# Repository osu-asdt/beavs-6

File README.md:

# BEAVS 6.7
BEAVS is a rocketry flight computer, with a comprehensive sensor suite and five servo channels.

## Features
- IMU
- Barometer
- Magnetometer
- Five 8.4V 10A servo channels with current monitoring
- Status LEDs
- Reverse polarity protection

## Parts
- RP2040 microcontroller
- ISM6HG256X IMU
- MS5607 barometer
- LIS2MDL magnetometer
- INA745 current monitors

## Pinout
| GPIO | Function            |
|------|---------------------|
|    0 | MISO                |
|    2 | SCK                 |
|    3 | MOSI                |
|    1 | Barometer CS        |
|    6 | IMU CS              |
|    4 | SDA                 |
|    5 | SCL                 |
|    7 | SD CMD              |
|    8 | SD DAT0             |
|    9 | SD DAT1             |
|   10 | SD DAT2             |
|   11 | SD DAT3             |
|   12 | SD CLK              |
|   14 | Expansion 1 (SDA)   |
|   15 | Expansion 2 (SCL)   |
|   13 | UART RX             |
|   16 | UART TX             |
|   17 | Servo power enable  |
|   28 | Efuse current       |
|   19 | Efuse status        |
|   27 | Servo 1             |
|   23 | Servo 2             |
|   24 | Servo 3             |
|   25 | Servo 4             |
|   26 | Servo 5             |
|   29 | Battery sense       |
|   22 | LED data            |
|   18 | Levelshift dir      |
|   21 | Arm switch          |

## Addresses
| Name             | Part     | I2C Address |
|------------------|----------|-------------|
| Magnetometer     | LIS2MDL  | 0x1e        |
| Servo 1 monitor  | INA745   | 0x40        |
| Servo 2 monitor  | INA745   | 0x41        |
| Servo 3 monitor  | INA745   | 0x43        |
| Servo 4 monitor  | INA745   | 0x44        |
| Servo 5 monitor  | INA745   | 0x45        |

## Notes
- The servo power enable pin is active high
- The boot and reset button on the board are enabled by the jumper J14 on the top right side of the board, this jumper must be removed before flight
- The servo pins are, from the center of the board to the edge, signal, ground, power
- The levelshift dir pin should be low in normal operation, and never floating
- The servo data pins and LED data pin should never be floating
- The arming switch should have an internal pullup, and closing the switch connects the pin to ground
- The battery sense pin is connected through a 100k-51k voltage divider, so the pin voltage is 0.3311 times the battery voltage
- Each servo channel can measure up to 39A, but continuous current shouldn't go much above 10A
- The total current consumption should be below 15A continuous
- The efuse current limit is set to 17.6A
- The addressable LEDs are WS2812-compatible, and they are chained as follows: status, magnetometer, barometer, IMU, SD
- The board can be configured to act as a USB host by swapping the CC resistors and adding a jumper, see the schematic

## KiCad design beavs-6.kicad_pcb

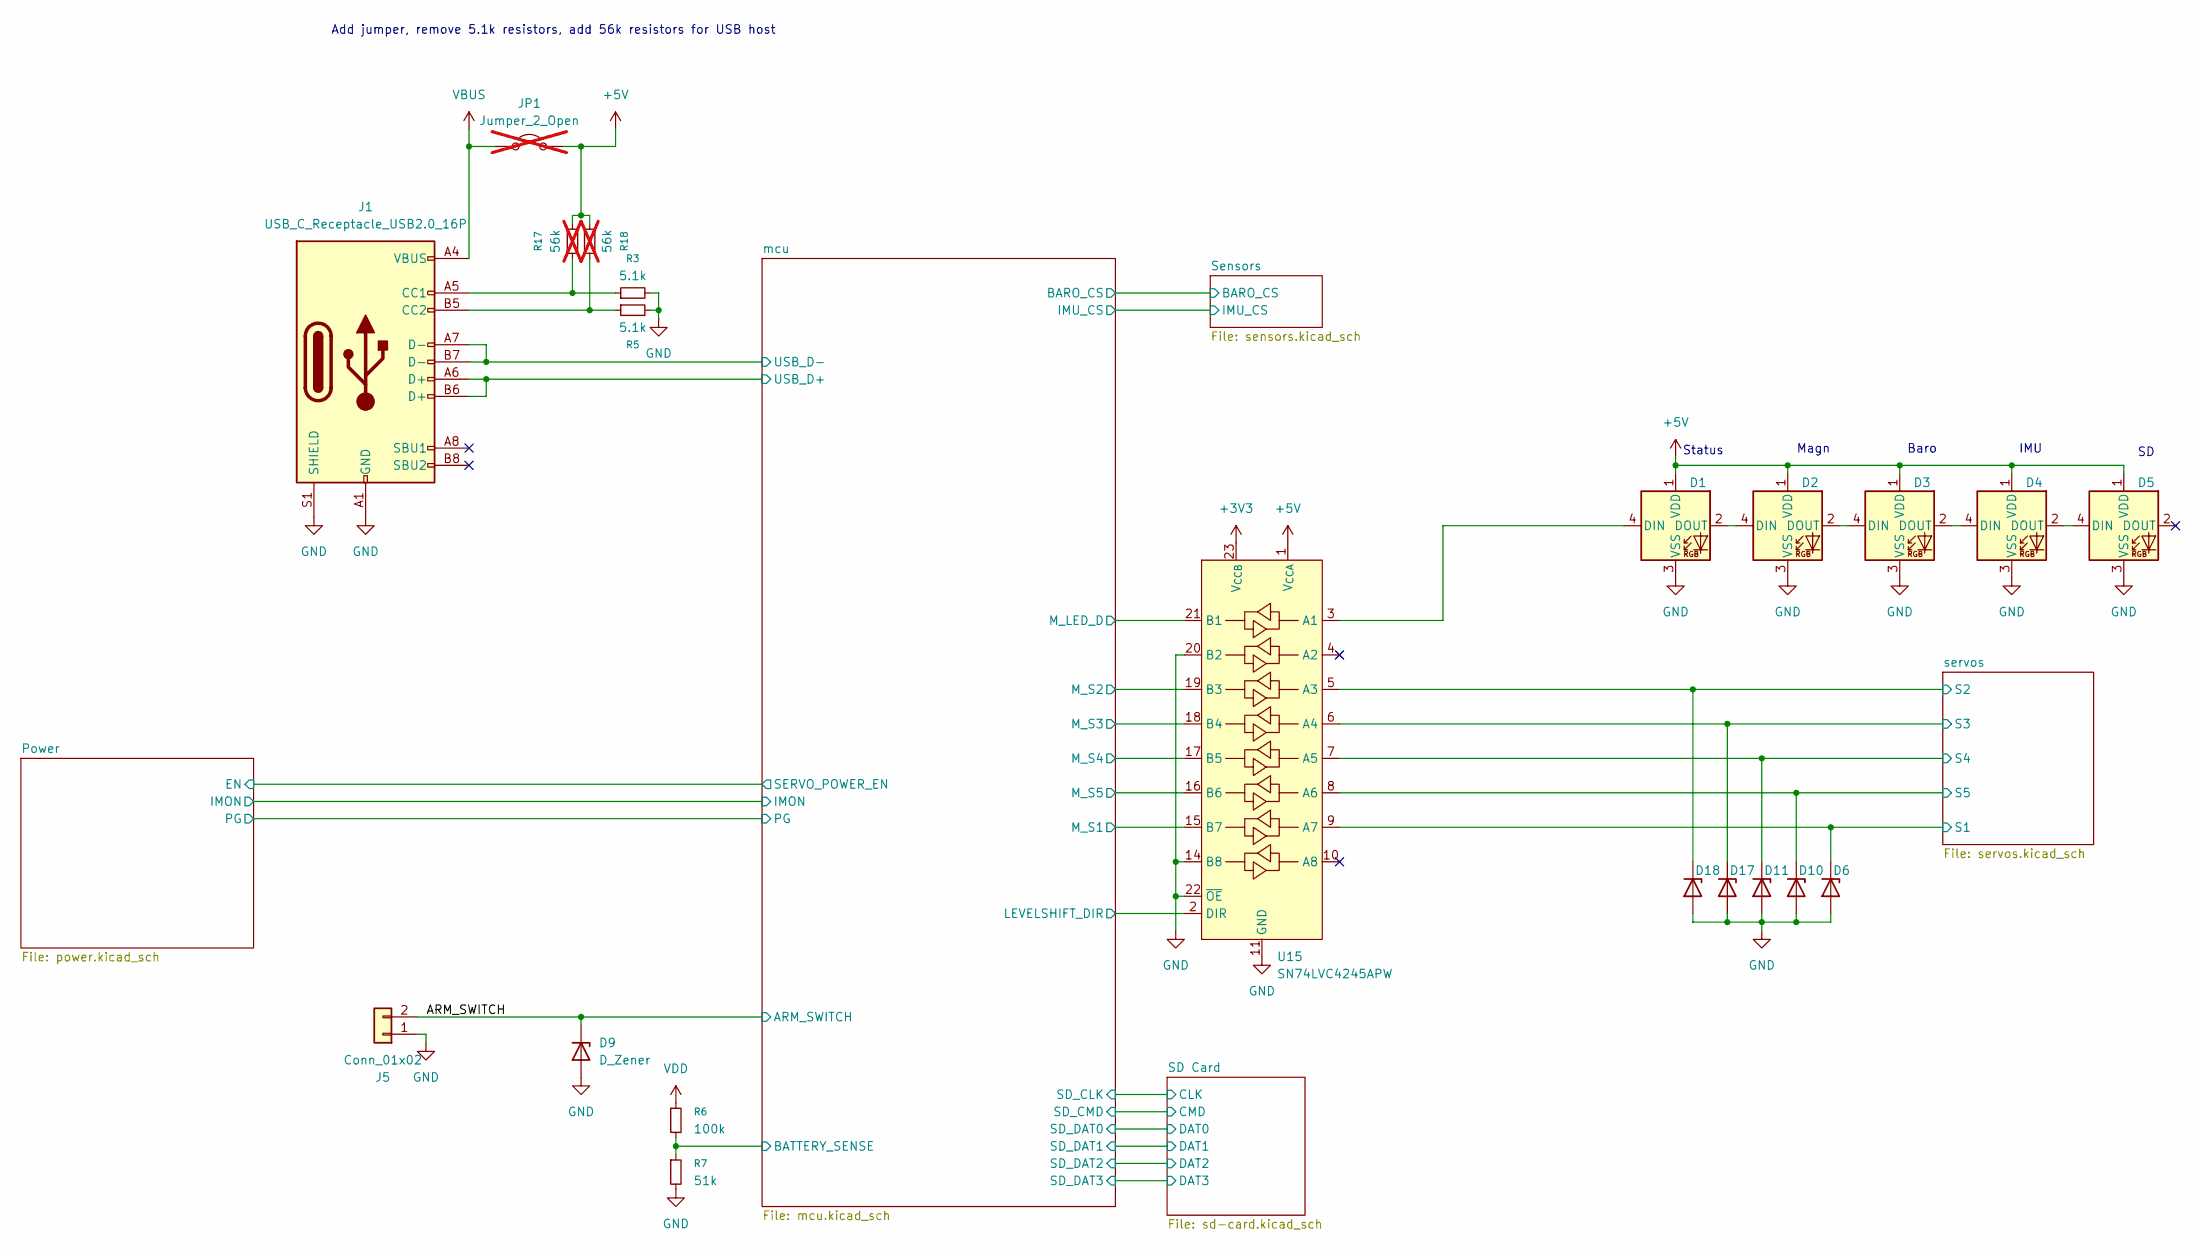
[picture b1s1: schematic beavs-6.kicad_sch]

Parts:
D1, D2, D3, D4, D5: SK6812-EC20; LED_SK6812-EC20_PLCC4_2.0x2.0mm; LCSC C2909058
D6, D10, D11, D17, D18: D_Zener; D_SOD-523; LCSC C20615819
D9: D_Zener; D_SOD-323; LCSC C20615801
J1: USB_C_Receptacle_USB2.0_16P; USB_C_Receptacle_G-Switch_GT-USB-7010ASV; LCSC C2988369
J5: Conn_01x02; JST_PH_B2B-PH-K_1x02_P2.00mm_Vertical; digikey 455-1704-ND
JP1: Jumper_2_Open; R_0402_1005Metric; not fitted
R3, R5: 5.1k; R_0402_1005Metric; LCSC C25905
R6: 100k; R_0402_1005Metric; LCSC C25741
R7: 51k; R_0402_1005Metric; LCSC C25794
R17, R18: 56k; R_0402_1005Metric; not fitted
U15: SN74LVC4245APW; TSSOP-24_4.4x7.8mm_P0.65mm; LCSC C7859

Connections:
+3V3: U15.23 (V_{CCB}), U15.24 (V_{CCB}); also elsewhere on the board
+5V: D1.1 (VDD), D2.1 (VDD), D3.1 (VDD), D4.1 (VDD), D5.1 (VDD), JP1.2 (B), R17.1, R18.1, U15.1 (V_{CCA}); also elsewhere on the board
/ARM_SWITCH: D9.1 (K), J5.2; also elsewhere on the board
/mcu/BATTERY_SENSE: R6.2, R7.1; also elsewhere on the board
/mcu/LEVELSHIFT_DIR: U15.2 (DIR); also elsewhere on the board
/mcu/M_LED_D: U15.21 (B1); also elsewhere on the board
/mcu/M_S1: U15.15 (B7); also elsewhere on the board
/mcu/M_S2: U15.19 (B3); also elsewhere on the board
/mcu/M_S3: U15.18 (B4); also elsewhere on the board
/mcu/M_S4: U15.17 (B5); also elsewhere on the board
/mcu/M_S5: U15.16 (B6); also elsewhere on the board
/mcu/USB_D+: J1.A6 (D+), J1.B6 (D+); also elsewhere on the board
/mcu/USB_D-: J1.A7 (D-), J1.B7 (D-); also elsewhere on the board
/servos/S1: D6.1 (K), U15.9 (A7); also elsewhere on the board
/servos/S2: D18.1 (K), U15.5 (A3); also elsewhere on the board
/servos/S3: D17.1 (K), U15.6 (A4); also elsewhere on the board
/servos/S4: D11.1 (K), U15.7 (A5); also elsewhere on the board
/servos/S5: D10.1 (K), U15.8 (A6); also elsewhere on the board
GND: D1.3 (VSS), D2.3 (VSS), D3.3 (VSS), D4.3 (VSS), D5.3 (VSS), D6.2 (A), D9.2 (A), D10.2 (A), D11.2 (A), D17.2 (A), D18.2 (A), J1.A1 (GND), J1.A12 (GND), J1.B1 (GND), J1.B12 (GND), J1.S1 (SHIELD), J5.1, R3.2, R5.2, R7.2, U15.11 (GND), U15.12 (GND), U15.13 (GND), U15.14 (B8), U15.20 (B2), U15.22 (~OE); also elsewhere on the board
unnamed: D1.4 (DIN), U15.3 (A1)
unnamed: D1.2 (DOUT), D2.4 (DIN)
unnamed: D2.2 (DOUT), D3.4 (DIN)
unnamed: D3.2 (DOUT), D4.4 (DIN)
unnamed: D4.2 (DOUT), D5.4 (DIN)
unnamed: J1.A5 (CC1), R3.1, R17.2
unnamed: J1.B5 (CC2), R5.1, R18.2
VBUS: J1.A4 (VBUS), J1.A9 (VBUS), J1.B4 (VBUS), J1.B9 (VBUS), JP1.1 (A); also elsewhere on the board
VDD: R6.1; also elsewhere on the board

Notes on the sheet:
Add jumper, remove 5.1k resistors, add 56k resistors for USB host
Baro
IMU
Status
Magn

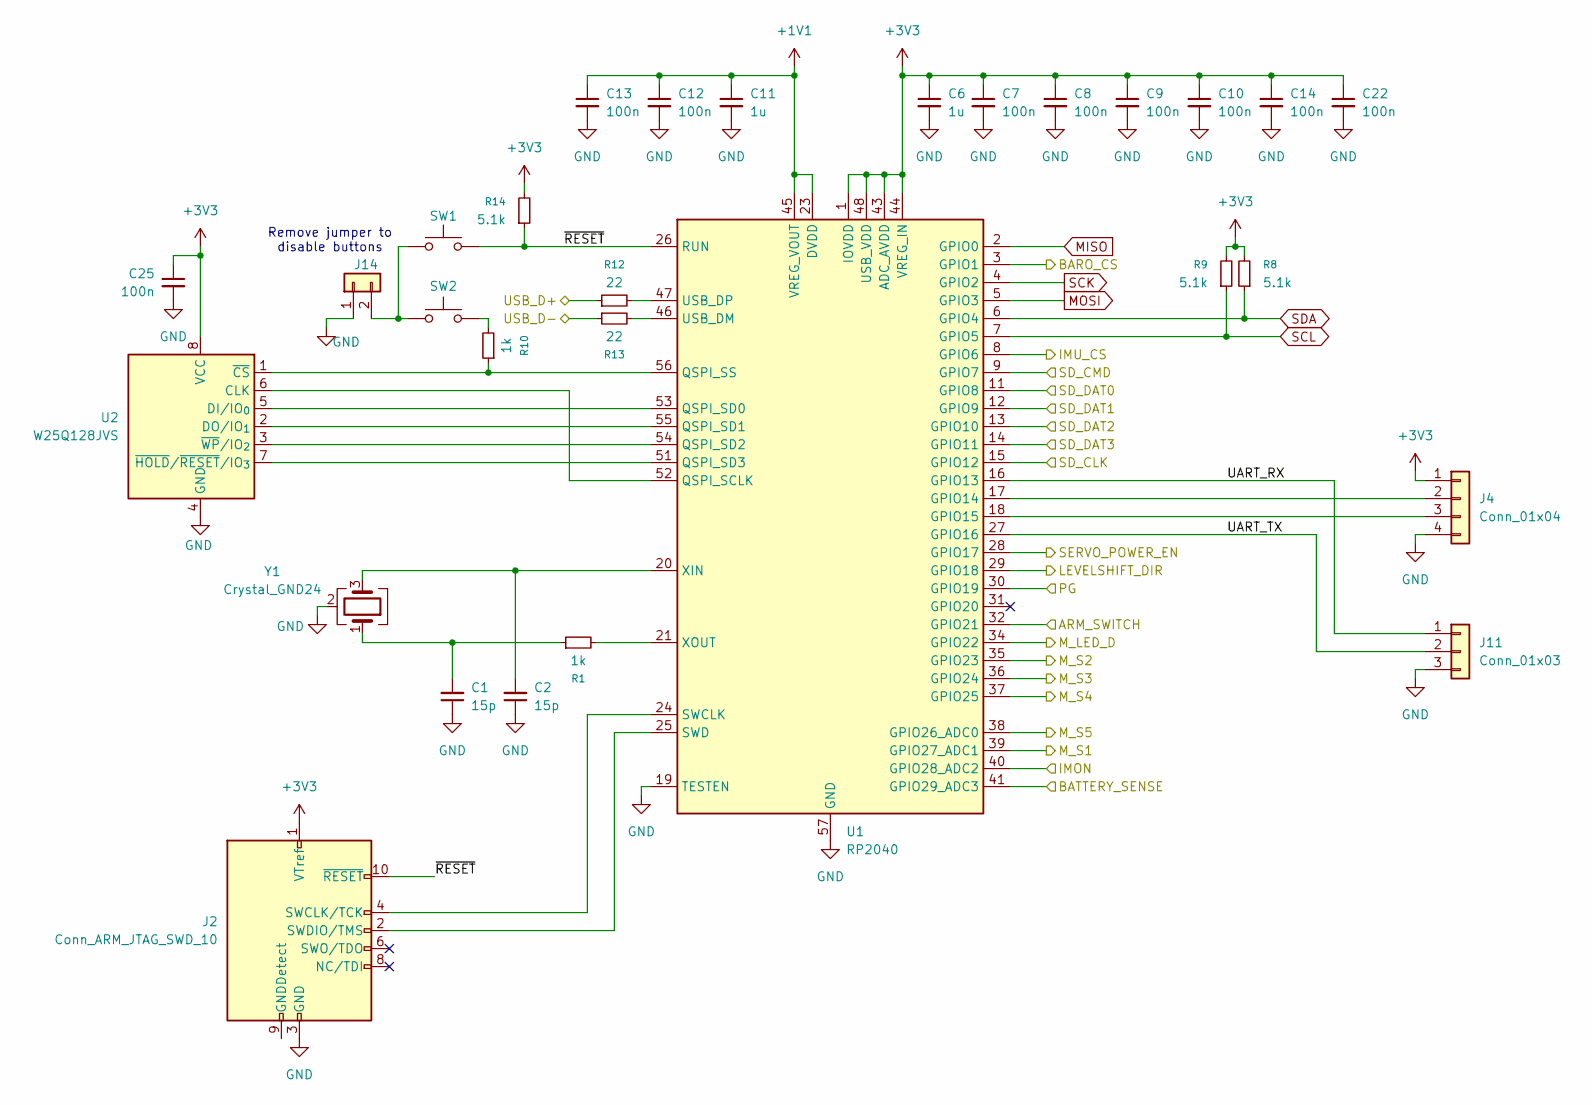
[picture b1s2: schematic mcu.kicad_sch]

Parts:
C1, C2: 15p; C_0402_1005Metric; LCSC C1548
C6, C11: 1u; C_0402_1005Metric; LCSC C52923
C7, C8, C9, C10, C12, C13, C14, C22, C25: 100n; C_0402_1005Metric; LCSC C1525
J2: Conn_ARM_JTAG_SWD_10; PinHeader_2x05_P1.27mm_Vertical_SMD; LCSC C5885449
J4: Conn_01x04; JST_PH_B4B-PH-K_1x04_P2.00mm_Vertical; digikey 455-1706-ND
J11: Conn_01x03; PinHeader_1x03_P2.54mm_Vertical
J14: Conn_01x02; PinHeader_1x02_P1.27mm_Vertical; digikey 952-3598-ND
R1, R10: 1k; R_0402_1005Metric; LCSC C11702
R8, R9, R14: 5.1k; R_0402_1005Metric; LCSC C25905
R12, R13: 22; R_0402_1005Metric; LCSC C25079
SW1, SW2: SW_Push; SW_SPST_TS-1088-AR02016; LCSC C720477
U1: RP2040; QFN-56-1EP_7x7mm_P0.4mm_EP3.2x3.2mm; LCSC C2040
U2: W25Q128JVS; SOIC-8_5.3x5.3mm_P1.27mm; LCSC C97521
Y1: Crystal_GND24; Crystal_SMD_Abracon_ABM8AIG-4Pin_3.2x2.5mm; LCSC C20625731

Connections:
+1V1: C11.1, C12.1, C13.1, U1.23 (DVDD), U1.45 (VREG_VOUT), U1.50 (DVDD)
+3V3: C6.1, C7.1, C8.1, C9.1, C10.1, C14.1, C22.1, C25.1, J2.1 (VTref), J4.1, R8.2, R9.2, R14.2, U1.1 (IOVDD), U1.10 (IOVDD), U1.22 (IOVDD), U1.33 (IOVDD), U1.42 (IOVDD), U1.43 (ADC_AVDD), U1.44 (VREG_IN), U1.48 (USB_VDD), U1.49 (IOVDD), U2.8 (VCC); also elsewhere on the board
/ARM_SWITCH: U1.32 (GPIO21); also elsewhere on the board
/Power/EN: U1.28 (GPIO17); also elsewhere on the board
/Power/IMON: U1.40 (GPIO28_ADC2); also elsewhere on the board
/Power/PG: U1.30 (GPIO19); also elsewhere on the board
/SD Card/CLK: U1.15 (GPIO12); also elsewhere on the board
/SD Card/CMD: U1.9 (GPIO7); also elsewhere on the board
/SD Card/DAT0: U1.11 (GPIO8); also elsewhere on the board
/SD Card/DAT1: U1.12 (GPIO9); also elsewhere on the board
/SD Card/DAT2: U1.13 (GPIO10); also elsewhere on the board
/SD Card/DAT3: U1.14 (GPIO11); also elsewhere on the board
/Sensors/BARO_CS: U1.3 (GPIO1); also elsewhere on the board
/Sensors/IMU_CS: U1.8 (GPIO6); also elsewhere on the board
/mcu/BATTERY_SENSE: U1.41 (GPIO29_ADC3); also elsewhere on the board
/mcu/LEVELSHIFT_DIR: U1.29 (GPIO18); also elsewhere on the board
/mcu/M_LED_D: U1.34 (GPIO22); also elsewhere on the board
/mcu/M_S1: U1.39 (GPIO27_ADC1); also elsewhere on the board
/mcu/M_S2: U1.35 (GPIO23); also elsewhere on the board
/mcu/M_S3: U1.36 (GPIO24); also elsewhere on the board
/mcu/M_S4: U1.37 (GPIO25); also elsewhere on the board
/mcu/M_S5: U1.38 (GPIO26_ADC0); also elsewhere on the board
/mcu/UART_RX: J11.1, U1.16 (GPIO13)
/mcu/UART_TX: J11.2, U1.27 (GPIO16)
/mcu/USB_D+: R12.1; also elsewhere on the board
/mcu/USB_D-: R13.1; also elsewhere on the board
/mcu/~RESET: J2.10 (~RESET), R14.1, SW1.2, U1.26 (RUN)
GND: C1.1, C2.1, C6.2, C7.2, C8.2, C9.2, C10.2, C11.2, C12.2, C13.2, C14.2, C22.2, C25.2, J2.3 (GND), J2.5 (GND), J4.4, J11.3, J14.1, U1.19 (TESTEN), U1.57 (GND), U2.4 (GND), Y1.2 (G), Y1.4 (G); also elsewhere on the board
MISO: U1.2 (GPIO0); also elsewhere on the board
MOSI: U1.5 (GPIO3); also elsewhere on the board
unnamed: C1.2, R1.1, Y1.1
unnamed: J2.4 (SWCLK/TCK), U1.24 (SWCLK)
unnamed: J2.2 (SWDIO/TMS), U1.25 (SWD)
unnamed: J4.2, U1.17 (GPIO14)
unnamed: J4.3, U1.18 (GPIO15)
unnamed: J14.2, SW1.1, SW2.1
unnamed: R10.2, SW2.2
unnamed: U1.52 (QSPI_SCLK), U2.6 (CLK)
unnamed: U1.53 (QSPI_SD0), U2.5 (DI/IO_{0})
unnamed: U1.55 (QSPI_SD1), U2.2 (DO/IO_{1})
unnamed: U1.54 (QSPI_SD2), U2.3 (~WP/IO_{2})
unnamed: U1.51 (QSPI_SD3), U2.7 (~HOLD/~RESET/IO_{3})
unnamed: R10.1, U1.56 (QSPI_SS), U2.1 (~CS)
unnamed: R13.2, U1.46 (USB_DM)
unnamed: R12.2, U1.47 (USB_DP)
unnamed: C2.2, U1.20 (XIN), Y1.3
unnamed: R1.2, U1.21 (XOUT)
SCK: U1.4 (GPIO2); also elsewhere on the board
SCL: R9.1, U1.7 (GPIO5); also elsewhere on the board
SDA: R8.1, U1.6 (GPIO4); also elsewhere on the board

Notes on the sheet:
Remove jumper to disable buttons

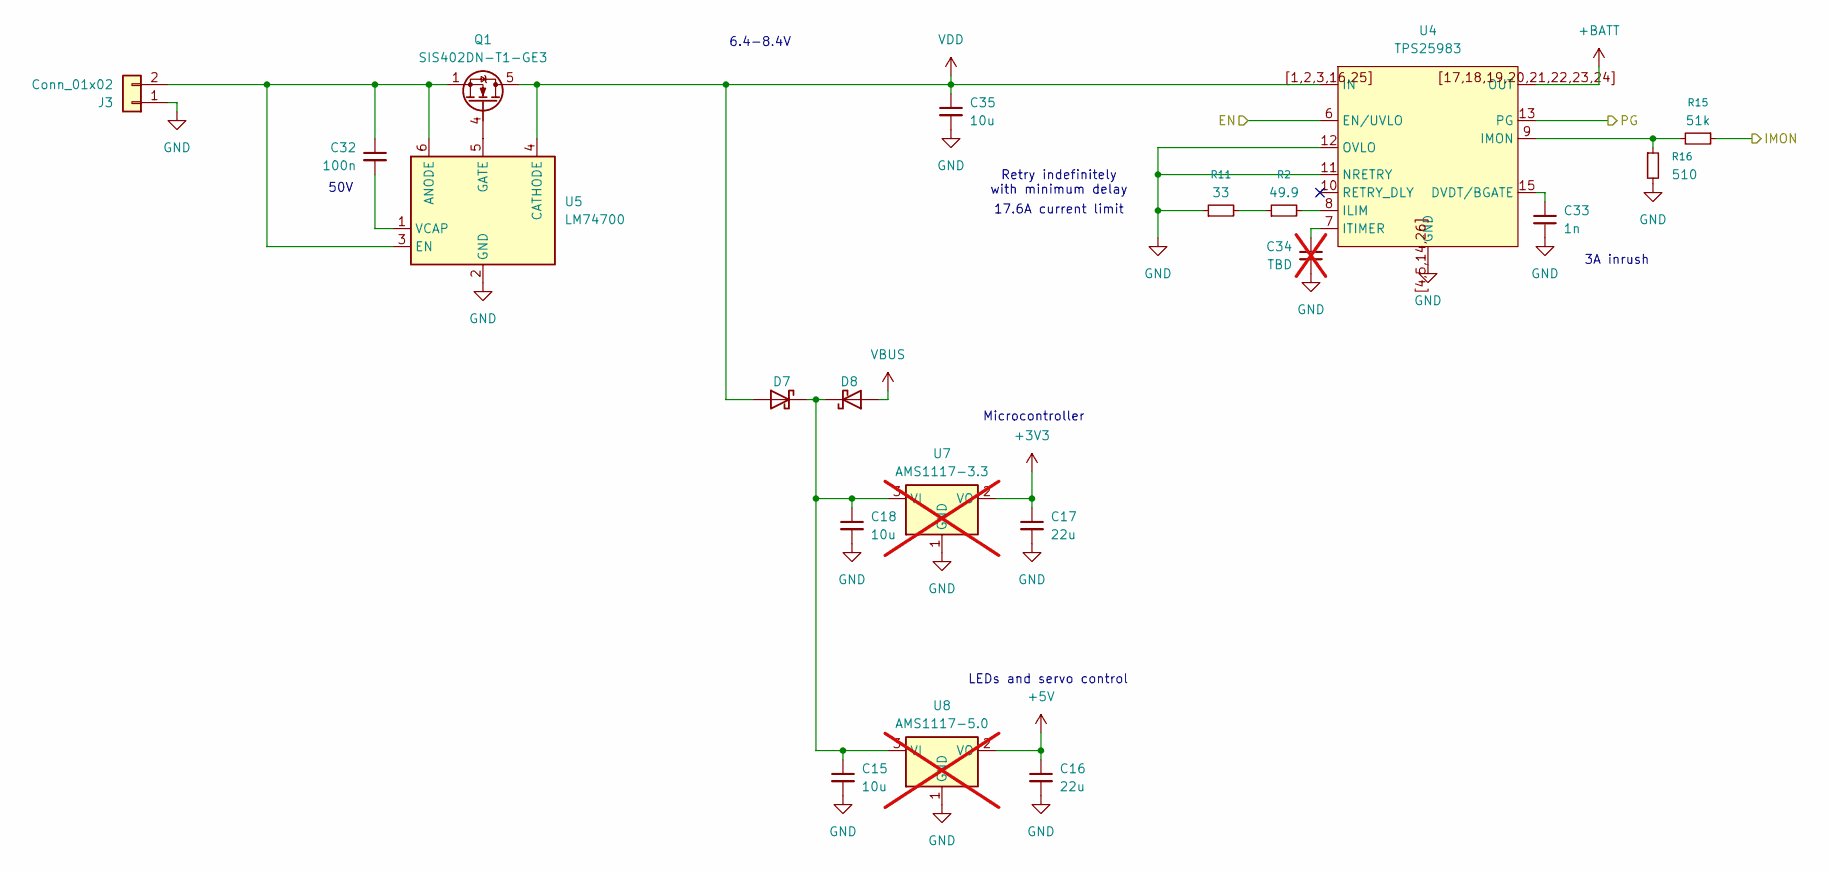
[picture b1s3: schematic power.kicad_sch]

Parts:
C15, C18, C35: 10u; C_0603_1608Metric; LCSC C19702
C16, C17: 22u; C_0603_1608Metric; LCSC C59461
C32: 100n; C_0603_1608Metric; LCSC C14663
C33: 1n; C_0402_1005Metric; LCSC C1523
C34: TBD; C_0402_1005Metric; not fitted
D7, D8: D_Schottky; D_SOD-123; LCSC C8598
J3: Conn_01x02; AMASS_XT30UPB-M_1x02_P5.0mm_Vertical
Q1: SIS402DN-T1-GE3; Vishay_PowerPAK_1212-8_Single; LCSC C15791
R2: 49.9; R_0402_1005Metric; LCSC C25120
R11: 33; R_0402_1005Metric; LCSC C25105
R15: 51k; R_0402_1005Metric; LCSC C25794
R16: 510; R_0402_1005Metric; LCSC C25123
U4: TPS25983; Texas_RGE0024M_QFN-24_4x4_Pitch0.5mm_2EP; LCSC C20607218
U5: LM74700; SOT-23-6; LCSC C2653623
U7: AMS1117-3.3; SOT-223-3_TabPin2; LCSC C6186; not fitted
U8: AMS1117-5.0; SOT-223-3_TabPin2; LCSC C6187; not fitted

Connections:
+3V3: C17.1, U7.2 (VO); also elsewhere on the board
+5V: C16.1, U8.2 (VO); also elsewhere on the board
+BATT: U4.17 (OUT), U4.18 (OUT), U4.19 (OUT), U4.20 (OUT), U4.21 (OUT), U4.22 (OUT), U4.23 (OUT), U4.24 (OUT); also elsewhere on the board
/Power/EN: U4.6 (EN/UVLO); also elsewhere on the board
/Power/IMON: R15.1; also elsewhere on the board
/Power/PG: U4.13 (PG); also elsewhere on the board
GND: C15.2, C16.2, C17.2, C18.2, C33.1, C34.1, C35.2, J3.1, R11.1, R16.2, U4.4 (GND), U4.5 (GND), U4.11 (NRETRY), U4.12 (OVLO), U4.14 (GND), U4.26 (GND), U4.[4,5,14,26] (GND), U5.2 (GND), U7.1 (GND), U8.1 (GND); also elsewhere on the board
unnamed: C15.1, C18.1, D7.1 (K), D8.1 (K), U7.3 (VI), U8.3 (VI)
unnamed: C32.1, J3.2, Q1.1 (S), Q1.2 (S), Q1.3 (S), U5.3 (EN), U5.6 (ANODE)
unnamed: Q1.4 (G), U5.5 (GATE)
unnamed: R2.1, R11.2
unnamed: C33.2, U4.15 (DVDT/BGATE)
unnamed: R2.2, U4.8 (ILIM)
unnamed: R15.2, R16.1, U4.9 (IMON)
unnamed: C34.2, U4.7 (ITIMER)
unnamed: C32.2, U5.1 (VCAP)
VBUS: D8.2 (A); also elsewhere on the board
VDD: C35.1, D7.2 (A), Q1.5 (D), U4.1 (IN), U4.2 (IN), U4.3 (IN), U4.16 (IN), U4.25 (IN), U4.[1,2,3,16,25] (IN), U5.4 (CATHODE); also elsewhere on the board

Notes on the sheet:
50V
Retry indefinitely with minimum delay
3A inrush
17.6A current limit
Microcontroller
6.4-8.4V
LEDs and servo control

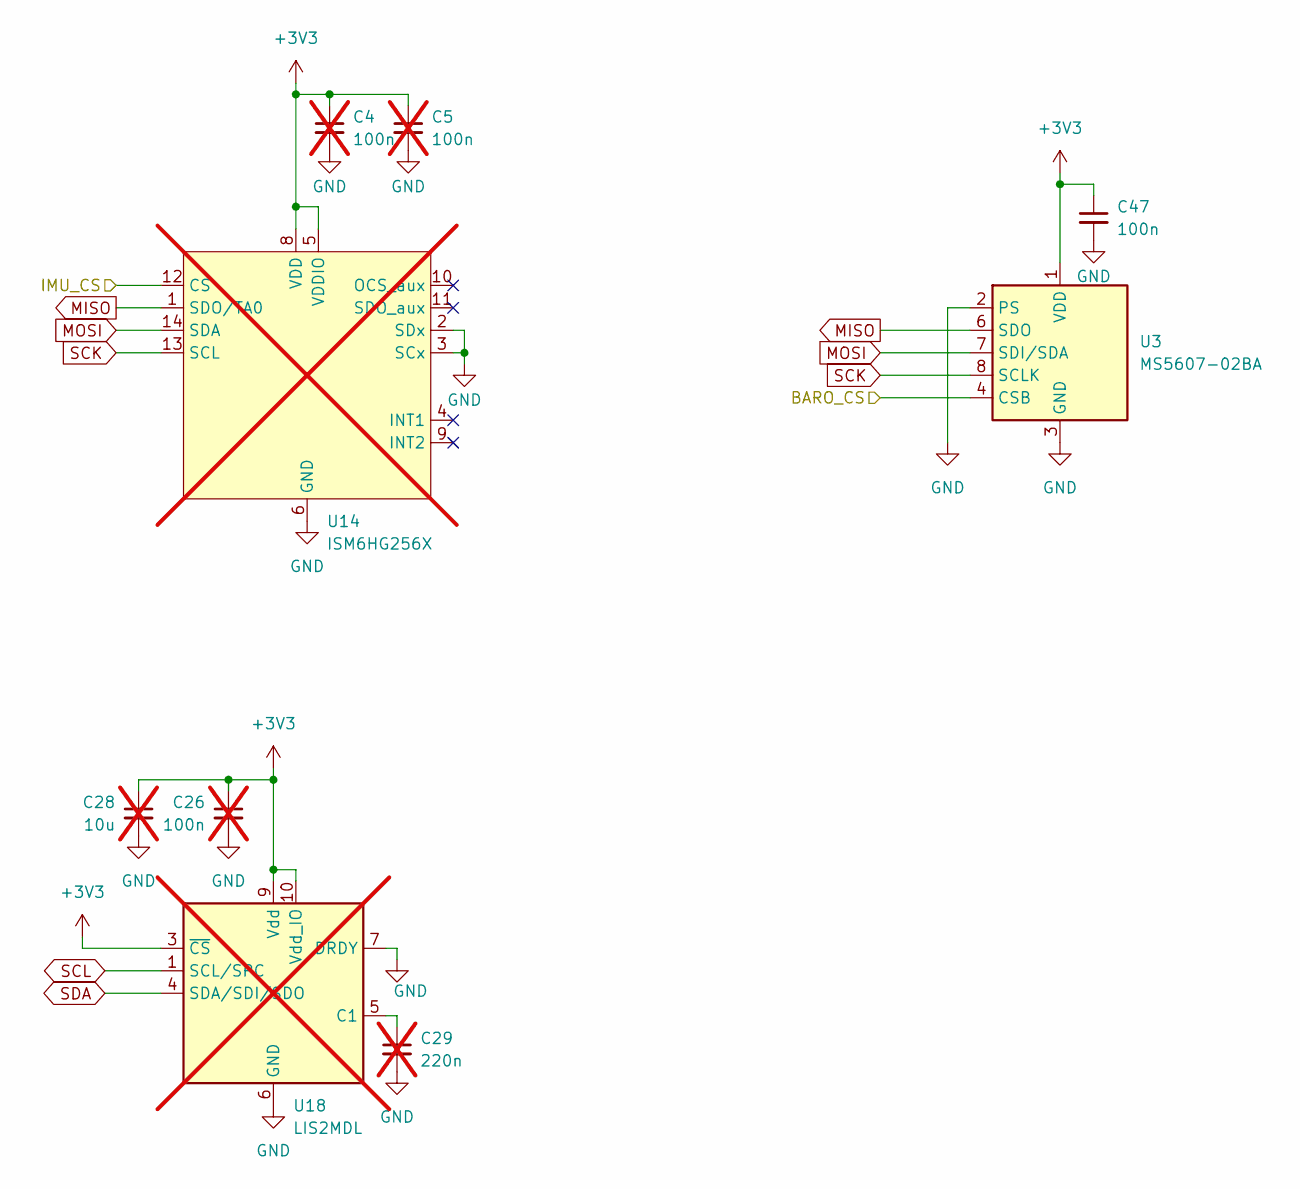
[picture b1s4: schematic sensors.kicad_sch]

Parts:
C4, C5, C26: 100n; C_0402_1005Metric; LCSC C1525; not fitted
C28: 10u; C_0402_1005Metric; LCSC C15525; not fitted
C29: 220n; C_0402_1005Metric; LCSC C16772; not fitted
C47: 100n; C_0402_1005Metric; LCSC C1525
U3: MS5607-02BA; LGA-8_3x5mm_P1.25mm; LCSC C97627
U14: ISM6HG256X; LGA-14_3x2.5mm_P0.5mm_LayoutBorder3x4y; digikey 497-ISM6HG256XTRCT-ND; not fitted
U18: LIS2MDL; LGA-12_2x2mm_P0.5mm; digikey 497-17588-1-ND; not fitted

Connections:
+3V3: C4.1, C5.1, C26.1, C28.1, C47.1, U3.1 (VDD), U14.5 (VDDIO), U14.8 (VDD), U18.3 (~CS), U18.9 (Vdd), U18.10 (Vdd_IO); also elsewhere on the board
/Sensors/BARO_CS: U3.4 (CSB), U3.5 (CSB); also elsewhere on the board
/Sensors/IMU_CS: U14.12 (CS); also elsewhere on the board
GND: C4.2, C5.2, C26.2, C28.2, C29.2, C47.2, U3.2 (PS), U3.3 (GND), U14.2 (SDx), U14.3 (SCx), U14.6 (GND), U14.7 (GND), U18.6 (GND), U18.7 (DRDY), U18.8 (GND); also elsewhere on the board
MISO: U3.6 (SDO), U14.1 (SDO/TA0); also elsewhere on the board
MOSI: U3.7 (SDI/SDA), U14.14 (SDA); also elsewhere on the board
unnamed: C29.1, U18.5 (C1)
SCK: U3.8 (SCLK), U14.13 (SCL); also elsewhere on the board
SCL: U18.1 (SCL/SPC); also elsewhere on the board
SDA: U18.4 (SDA/SDI/SDO); also elsewhere on the board

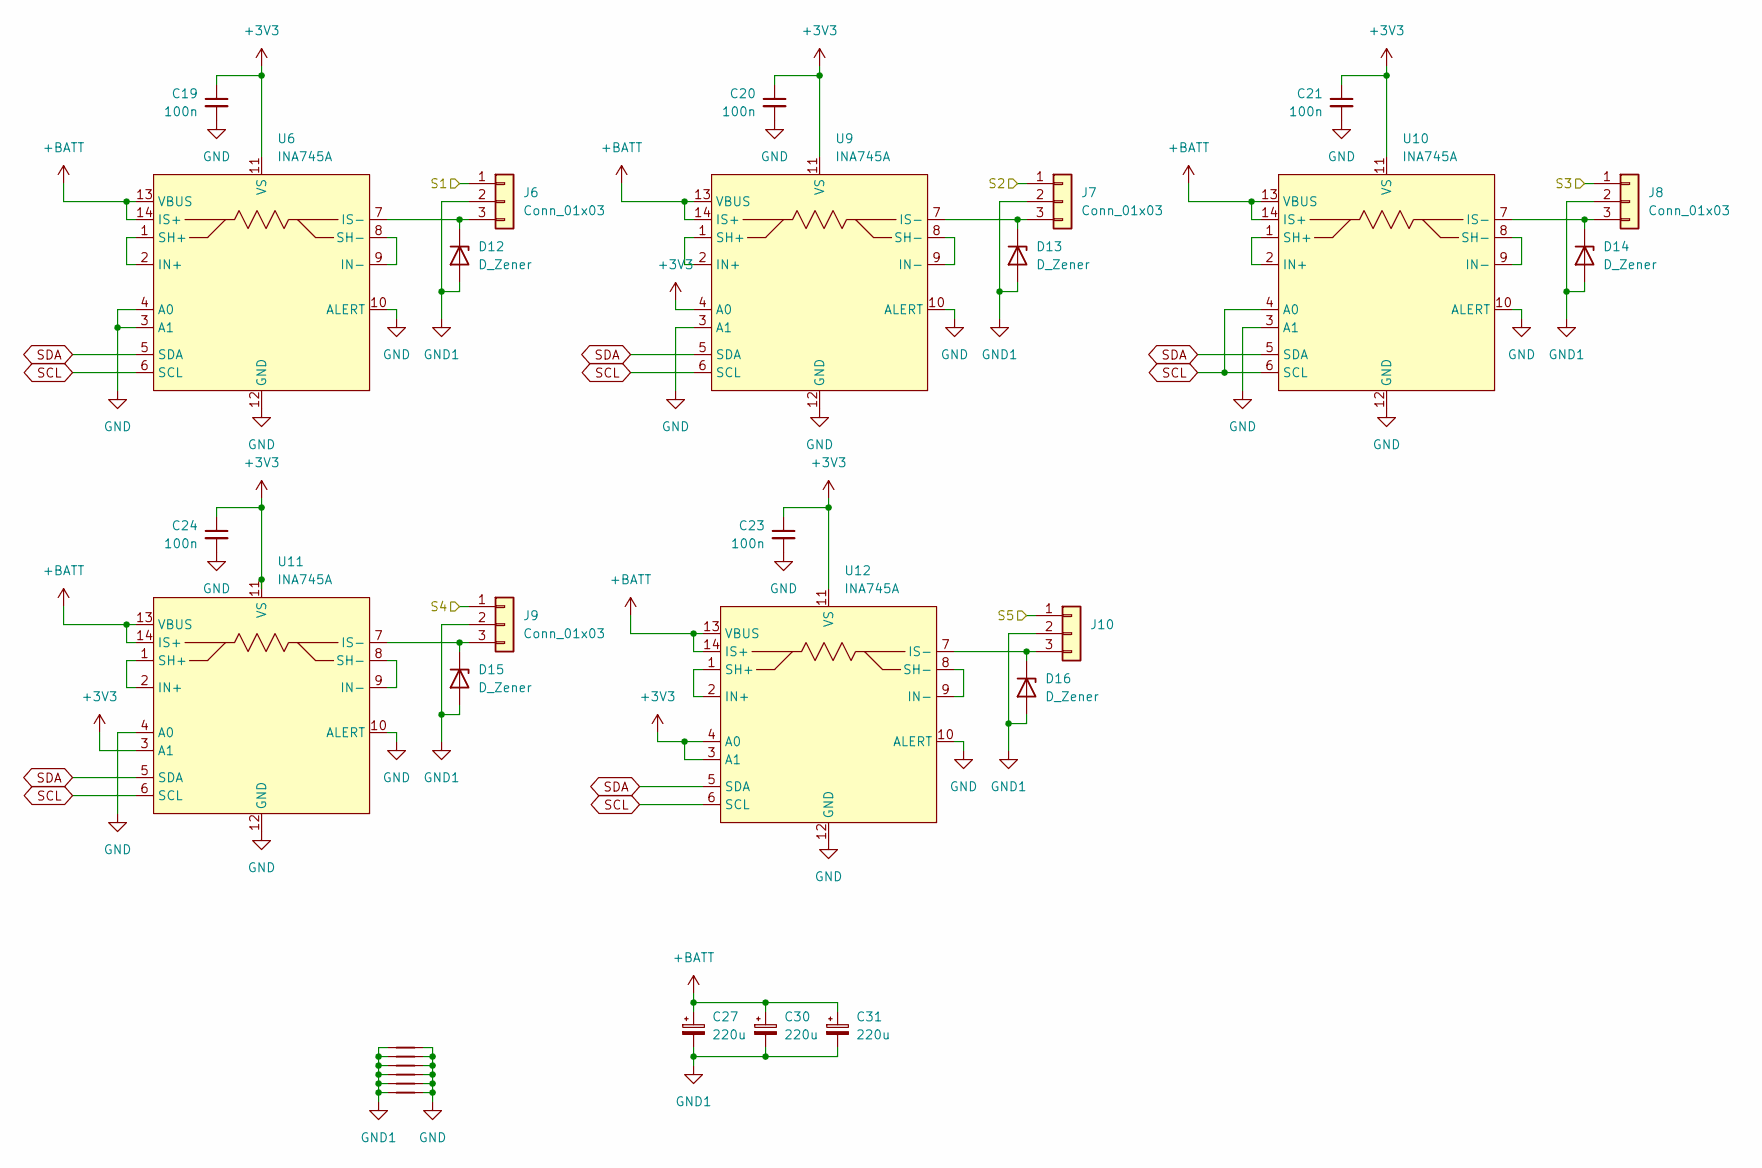
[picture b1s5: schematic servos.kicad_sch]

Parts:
C19, C20, C21, C23, C24: 100n; C_0402_1005Metric; LCSC C1525
C27, C30, C31: 220u; CP_Radial_D5.0mm_P2.00mm; digikey 399-ESK227M010AC3AA-ND
D12, D13, D14, D15, D16: D_Zener; D_SOD-523; LCSC C20615819
J6, J7, J8, J9, J10: Conn_01x03; JST_VH_B3P-VH-B_1x03_P3.96mm_Vertical_model; digikey 455-B3P-VH-ND
NT1, NT2, NT3, NT4: NetTie_2; NetTie-2_SMD_Pad2.0mm
NT5, NT6: NetTie_2; NetTie-2_SMD_Pad0.5mm
U6, U9, U10, U11, U12: INA745A; QFN-14-REL_TI; LCSC C35213810

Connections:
+3V3: C19.1, C20.1, C21.1, C23.1, C24.1, U6.11 (VS), U9.4 (A0), U9.11 (VS), U10.11 (VS), U11.3 (A1), U11.11 (VS), U12.3 (A1), U12.4 (A0), U12.11 (VS); also elsewhere on the board
+BATT: C27.1, C30.1, C31.1, U6.13 (VBUS), U6.14 (IS+), U9.13 (VBUS), U9.14 (IS+), U10.13 (VBUS), U10.14 (IS+), U11.13 (VBUS), U11.14 (IS+), U12.13 (VBUS), U12.14 (IS+); also elsewhere on the board
/servos/S1: J6.1; also elsewhere on the board
/servos/S2: J7.1; also elsewhere on the board
/servos/S3: J8.1; also elsewhere on the board
/servos/S4: J9.1; also elsewhere on the board
/servos/S5: J10.1; also elsewhere on the board
GND: C19.2, C20.2, C21.2, C23.2, C24.2, NT1.2, NT2.2, NT3.2, NT4.2, NT5.2, NT6.2, U6.3 (A1), U6.4 (A0), U6.10 (ALERT), U6.12 (GND), U9.3 (A1), U9.10 (ALERT), U9.12 (GND), U10.3 (A1), U10.10 (ALERT), U10.12 (GND), U11.4 (A0), U11.10 (ALERT), U11.12 (GND), U12.10 (ALERT), U12.12 (GND); also elsewhere on the board
GND1: C27.2, C30.2, C31.2, D12.2 (A), D13.2 (A), D14.2 (A), D15.2 (A), D16.2 (A), J6.2, J7.2, J8.2, J9.2, J10.2, NT1.1, NT2.1, NT3.1, NT4.1, NT5.1, NT6.1
unnamed: D12.1 (K), J6.3, U6.7 (IS-)
unnamed: D13.1 (K), J7.3, U9.7 (IS-)
unnamed: D14.1 (K), J8.3, U10.7 (IS-)
unnamed: D15.1 (K), J9.3, U11.7 (IS-)
unnamed: D16.1 (K), J10.3, U12.7 (IS-)
unnamed: U6.1 (SH+), U6.2 (IN+)
unnamed: U6.8 (SH-), U6.9 (IN-)
unnamed: U9.1 (SH+), U9.2 (IN+)
unnamed: U9.8 (SH-), U9.9 (IN-)
unnamed: U10.1 (SH+), U10.2 (IN+)
unnamed: U10.8 (SH-), U10.9 (IN-)
unnamed: U11.1 (SH+), U11.2 (IN+)
unnamed: U11.8 (SH-), U11.9 (IN-)
unnamed: U12.1 (SH+), U12.2 (IN+)
unnamed: U12.8 (SH-), U12.9 (IN-)
SCL: U6.6 (SCL), U9.6 (SCL), U10.4 (A0), U10.6 (SCL), U11.6 (SCL), U12.6 (SCL); also elsewhere on the board
SDA: U6.5 (SDA), U9.5 (SDA), U10.5 (SDA), U11.5 (SDA), U12.5 (SDA); also elsewhere on the board

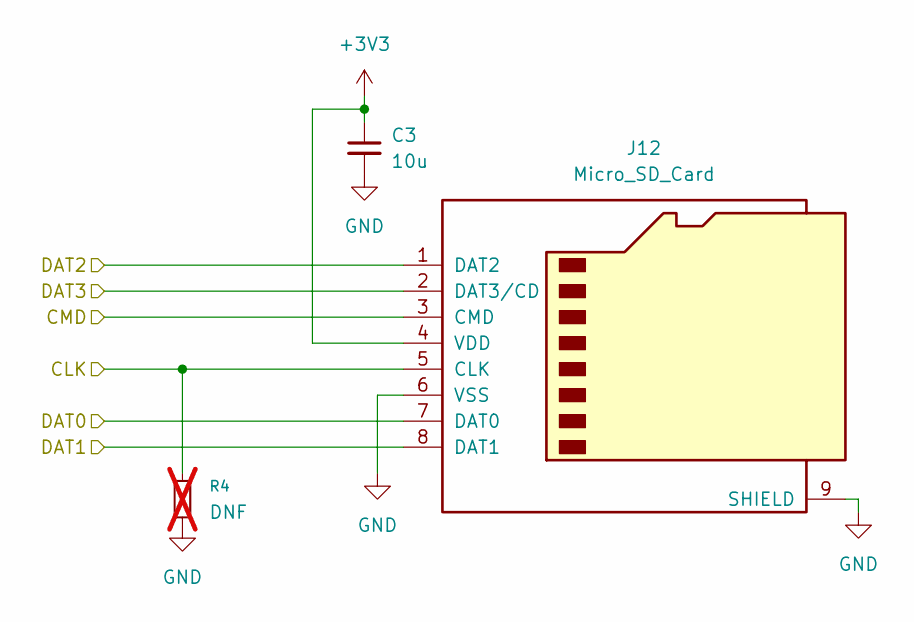
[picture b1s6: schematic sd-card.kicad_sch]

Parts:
C3: 10u; C_0402_1005Metric; LCSC C15525
J12: Micro_SD_Card; microSD_HC_Molex_47219-2001; LCSC C164170
R4: DNF; R_0402_1005Metric; not fitted

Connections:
+3V3: C3.1, J12.4 (VDD); also elsewhere on the board
/SD Card/CLK: J12.5 (CLK), R4.1; also elsewhere on the board
/SD Card/CMD: J12.3 (CMD); also elsewhere on the board
/SD Card/DAT0: J12.7 (DAT0); also elsewhere on the board
/SD Card/DAT1: J12.8 (DAT1); also elsewhere on the board
/SD Card/DAT2: J12.1 (DAT2); also elsewhere on the board
/SD Card/DAT3: J12.2 (DAT3/CD); also elsewhere on the board
GND: C3.2, J12.6 (VSS), J12.9 (SHIELD), R4.2; also elsewhere on the board

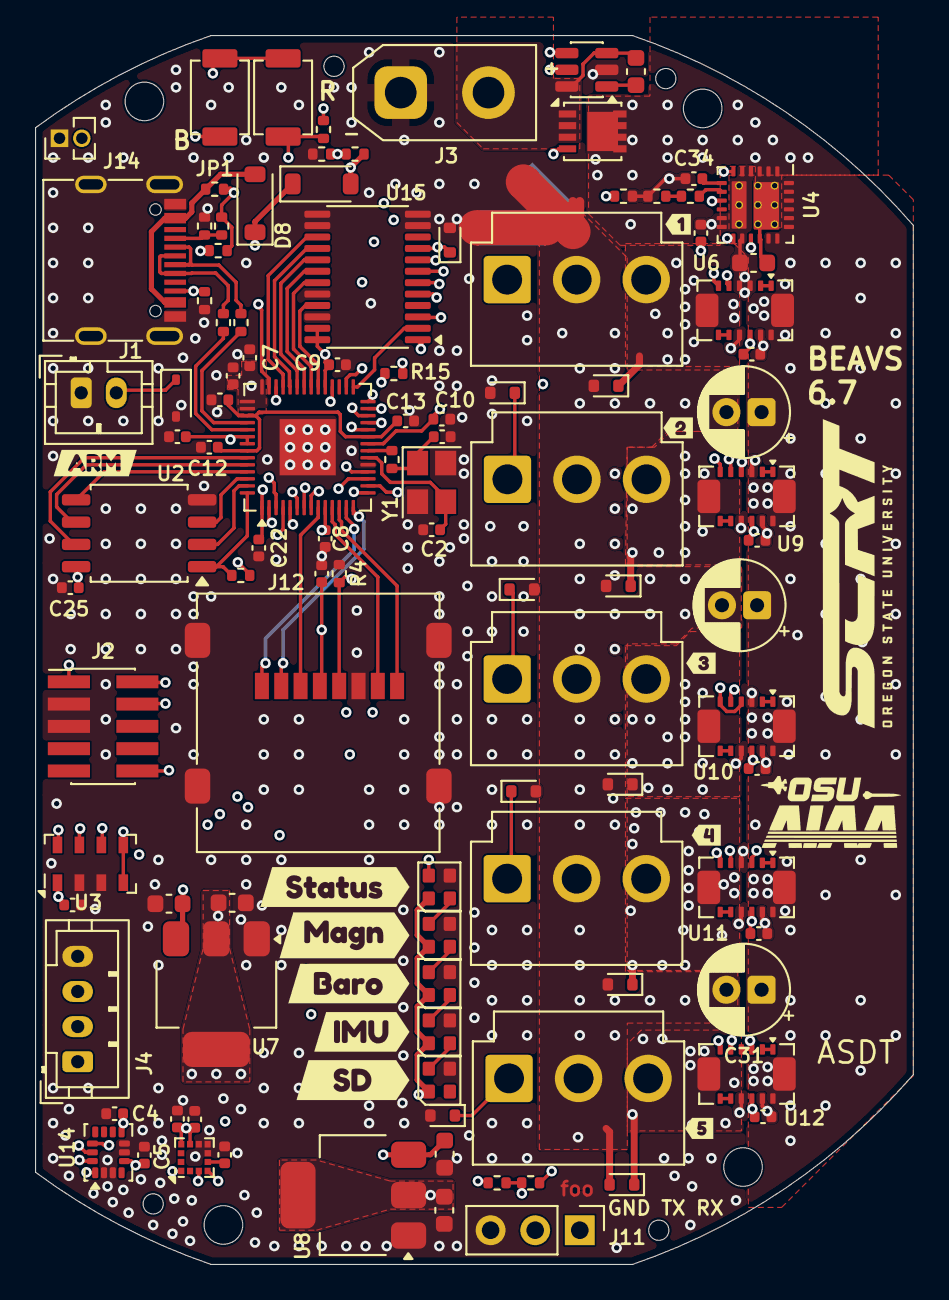
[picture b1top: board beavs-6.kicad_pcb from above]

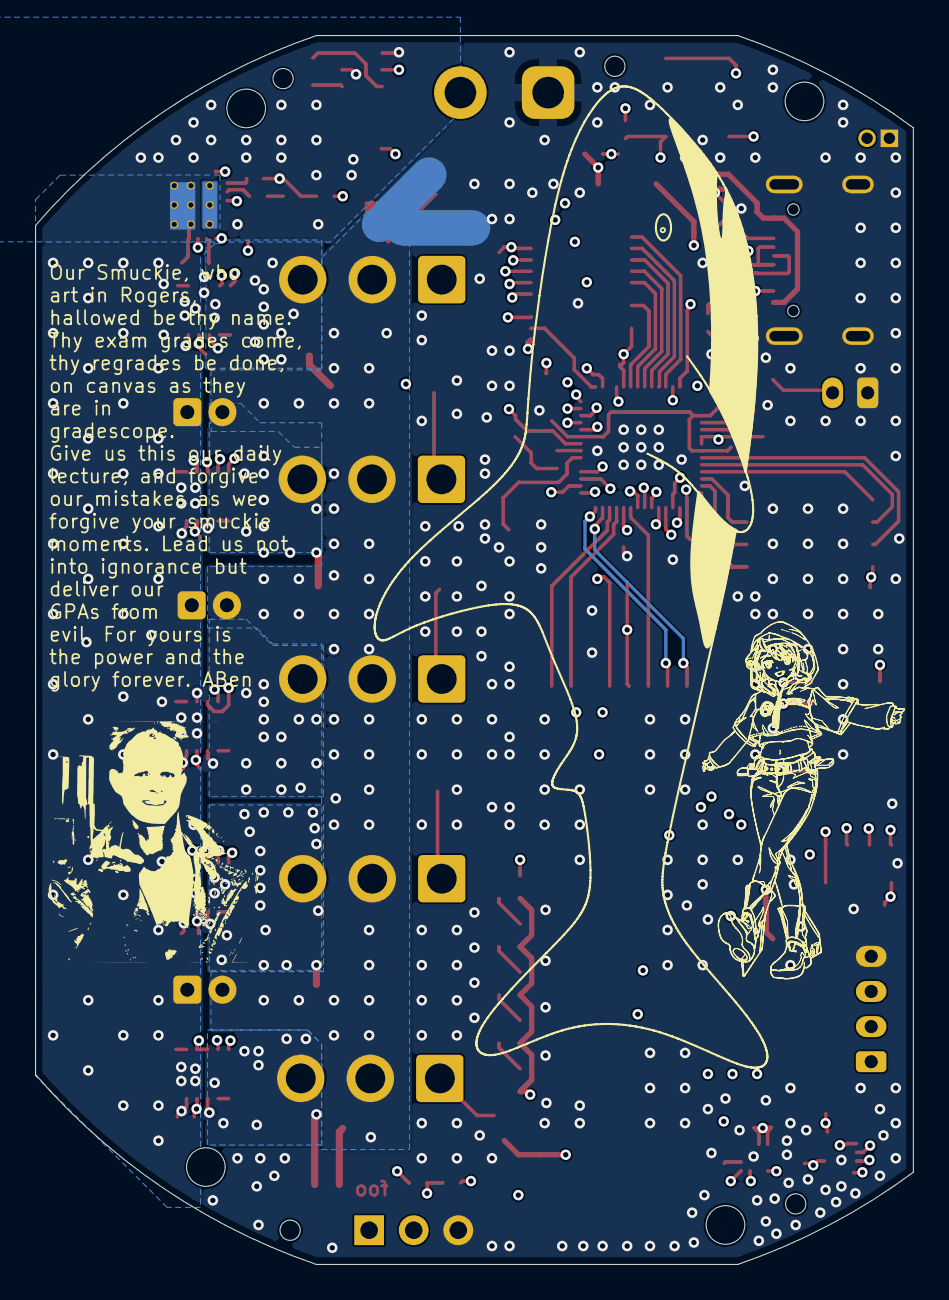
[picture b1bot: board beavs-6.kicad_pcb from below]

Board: 4 copper layers, 50.0 x 70.0 mm, 122 parts (2 on the bottom side), 92 nets.

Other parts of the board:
kibuzzard-6ACD650F: G***; kibuzzard-6ACD650F
kibuzzard-6ACFDF65: G***; kibuzzard-6ACFDF65
kibuzzard-6930C9BE: G***; kibuzzard-6930C9BE
kibuzzard-6930C9FF: G***; kibuzzard-6930C9FF
kibuzzard-6945FB0B: G***; kibuzzard-6945FB0B
kibuzzard-6945FB1F: G***; kibuzzard-6945FB1F
kibuzzard-6945FB15: G***; kibuzzard-6945FB15
kibuzzard-6945FB28: G***; kibuzzard-6945FB28
kibuzzard-6945FB30: G***; kibuzzard-6945FB30
kibuzzard-693096D7: G***; kibuzzard-693096D7
kibuzzard-69309760: G***; kibuzzard-69309760

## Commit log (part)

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2025-11-21 do some schematic work
2025-11-21 got it to fit in about the right shape
2025-11-21 importing CAD edge cuts
2025-11-22 add 3d models and do other stuff
2025-11-23 add some TVS diodes
2025-11-25 update schematics and add 3d models
2025-11-27 cleanup
2025-12-03 change out LEDs, add silk, start getting ready for fab
2025-12-04 stapling vias, silk, minor schematic tweaks
2025-12-04 capacitor spam, needs current limiting
2025-12-04 moved to ideal diode + back to back FETs
2025-12-05 bad inrush limiting
2025-12-05 I may be stupid
2025-12-05 definitely stupid
2025-12-05 swapped to a reverse polarity + inrush scheme that might actually work
2025-12-06 finished power, checked most sensor schematics
2025-12-06 gitignore
2025-12-07 bigger pours for FETs, various cleanup, switching to different level shifter
2025-12-08 changes apparently but idk what
2025-12-09 switched around some footprints, added expansion header
2025-12-12 Minor tweaks
2025-12-20 switched to global labels for SPI and I2C, added labels for servos
2026-01-08 add reset pullup...
2026-01-09 various tweaks
2026-01-09 fix pin order on FETs, cleanup
2026-01-09 switching to electrolytic caps
2026-01-10 final tweaks
2026-01-10 final revision, sending to fab
2026-01-10 blunkinator
2026-01-11 rename
2026-01-11 readme
2026-01-15 add schematic PDF, improve schematic readability
